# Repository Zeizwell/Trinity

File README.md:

# ZX Trinity

**Sound card for the ZX Spectrum: Atari, Amiga and MSX on one board.** For ZX-BUS / NemoBus and ZX Evolution.

| | |
|---|---|
| AY | 2 × AY-3-8910 / YM2149F in sockets, TurboSound (chip select `#FF` / `#FE`), ports `#FFFD` / `#BFFD` |
| AYFX | timer effects on the real AY chips: SID, Sync, FM, Env FM, PWM (16 steps 0..50 %, sweep) |
| SNDH | Atari ST music player: 68000 at 8 MHz on the card, sound on the real AY chips |
| GS | General Sound interface (`#B3` / `#BB`); NeoGS - in progress |
| Tracker modules | MOD (ProTracker), S3M, XM up to 32 channels; IT - in progress |
| Amiga | Paula A500 / A1200, BLEP, LED filter; presets Clean, A500, A1200, HiFi, Custom |
| MSX | Moonsound OPL4, MIDI (GM) - in progress |
| DAC | PCM5102A, I2S 32 bit |
| Output | 3.5 mm line out: AY through an OPA1656 mixer, DAC directly; narrow stereo - DIP switch |
| Processors | 2 × RP2350B (16 MB flash, 8 MB PSRAM each), CPLD EPM3128 with its own 32 MHz clock |
| Storage | microSD |
| Screen | any SPI TFT module on a cable: scopes, levels, what is playing, chip status, temperature, firmware versions |

## Paula

| | |
|---|---|
| Channels | 4, samples 8 bit signed |
| Rate | own per channel: note period at 3.55 MHz (PAL), no common output rate |
| Signal | steps (zero-order hold), sample never resampled; steps band-limited: minBLEP 16 × 16 |
| Volume | 0..64; 6-bit PWM - option, off by default |
| Stereo | hard: 0 + 3 left, 1 + 2 right |
| Filters (board values) | A500: low-pass 1st order 4.4 kHz; LED: low-pass 2nd order 3.1 kHz, Q 0.66, on the fly (`E0x`); high-pass ~5 Hz; A1200: no 4.4 kHz |
| Modes | Clean, A500, A1200, HiFi (cubic), Custom - on the fly |
| ProTracker | replayer one to one, PT quirks kept; Paula registers = pt2-clone on 80,595 modules |

## Status

### Done
- Board rev A2: schematic, placement and routing done, DRC clean; next - Gerbers and order (rev A1 was made, but unusable: edge connector defect)
- S3M player: matches OpenMPT on 8,394 of 8,459 modules (99.2 %); XM player (up to 32 channels): 35,160 of 35,458 (99.2 %) (on PC, every song played to the end)
- General Sound: ports, loading modules and effects, commands (tested without a Spectrum)
- Z80 API and SDK: find the card, settings, presets, CPU load, filter curves, versions
- CPLD firmware, first version: 91 of 128 macrocells, testbench passes; not yet on hardware

### Works on a test setup (ZX Evolution + RP2350 board)
- AY part: registers and timer effects; the FT2 tracker finds the card and uses the effects
- SNDH player: the Spectrum only sends the file. Wild Commander plugin: play, pause, seek, next track

### To do
- Build the first boards and test on a real Spectrum, CPLD on hardware
- Firmware updates from SD, driver program for the Spectrum
- OPL4, MIDI, NeoGS, IT player; XM: filters (`Zxx`), more than 32 channels
- CPU clock modes Economy / Normal / Turbo
- Output up to 96 kHz
- Trinity player program: all card modes, channel and pattern view, bass / treble

---

# ZX Trinity

**Звуковая карта для ZX Spectrum: Atari, Amiga и MSX на одной плате.** Для ZX-BUS / NemoBus и ZX Evolution.

| | |
|---|---|
| AY | 2 × AY-3-8910 / YM2149F на панельках, TurboSound (выбор чипа `#FF` / `#FE`), порты `#FFFD` / `#BFFD` |
| AYFX | таймерные эффекты на настоящих AY: SID, Sync, FM, Env FM, PWM (16 ступеней 0..50 %, свип) |
| SNDH | плеер музыки Atari ST: 68000 на 8 МГц на карте, звук на настоящих AY |
| GS | интерфейс General Sound (`#B3` / `#BB`); NeoGS - в работе |
| Трекерные модули | MOD (ProTracker), S3M, XM до 32 каналов; IT - в работе |
| Amiga | Paula A500 / A1200, BLEP, LED-фильтр; пресеты Clean, A500, A1200, HiFi, Custom |
| MSX | Moonsound OPL4, MIDI (GM) - в работе |
| ЦАП | PCM5102A, I2S 32 бита |
| Выход | линия 3.5 мм: AY через сумматор на OPA1656, ЦАП напрямую; узкое стерео - DIP-переключатель |
| Процессоры | 2 × RP2350B (флеш 16 МБ, PSRAM 8 МБ у каждого), CPLD EPM3128 со своим генератором 32 МГц |
| Носитель | microSD |
| Экран | любой SPI TFT-модуль на проводах: осциллографы, уровни, что играет, состояние чипов, температура, версии прошивок |

## Paula

| | |
|---|---|
| Каналы | 4, сэмплы 8 бит со знаком |
| Частота | своя у каждого канала: период ноты на 3.55 МГц (PAL), общей частоты вывода нет |
| Сигнал | ступеньки (удержание отсчёта), сэмпл не пересчитывается; ступеньки с ограниченной полосой: minBLEP 16 × 16 |
| Громкость | 0..64; ШИМ 6 бит - опция, по умолчанию выключен |
| Стерео | жёсткое: 0 + 3 слева, 1 + 2 справа |
| Фильтры (номиналы плат) | A500: ФНЧ 1-го порядка 4.4 кГц; LED: ФНЧ 2-го порядка 3.1 кГц, Q 0.66, на лету (`E0x`); ФВЧ ~5 Гц; A1200: без 4.4 кГц |
| Режимы | Clean, A500, A1200, HiFi (кубическая), Custom - на лету |
| ProTracker | реплеер один в один, причуды PT сохранены; регистры Paula = pt2-clone на 80 595 модулях |

## Что сейчас

### Готово
- Плата рев A2: схема, расстановка и разводка готовы, DRC чистый; дальше - гербера и заказ (рев A1 изготовлена, но не годится: брак разъёма шины)
- Плеер S3M: совпал с OpenMPT на 8 394 из 8 459 модулей (99.2 %); плеер XM (до 32 каналов): 35 160 из 35 458 (99.2 %) (на ПК, каждая песня до конца)
- General Sound: порты, загрузка модулей и эффектов, команды (проверено без Спектрума)
- API и SDK для Z80: поиск карты, настройки, пресеты, нагрузка, кривые фильтров, версии
- Прошивка CPLD, первая версия: 91 из 128 макроячеек, тест на модели проходит; на железе ещё нет

### Работает на макете (ZX Evolution + плата RP2350)
- Часть AY: регистры и таймерные эффекты; трекер FT2 находит карту и пользуется эффектами
- Плеер SNDH: Спектрум только отдаёт файл. Плагин для Wild Commander: игра, пауза, перемотка, следующий трек

### Дальше
- Собрать первые платы и проверить на настоящем Спектруме, CPLD на железе
- Обновление прошивок с SD, программа-драйвер для Спектрума
- OPL4, MIDI, NeoGS, плеер IT; XM: фильтры (`Zxx`), больше 32 каналов
- Режимы частоты процессора Эконом / Нормал / Турбо
- Вывод до 96 кГц
- Программа-плеер Trinity: все режимы карты, вид каналов и паттерна, НЧ / ВЧ

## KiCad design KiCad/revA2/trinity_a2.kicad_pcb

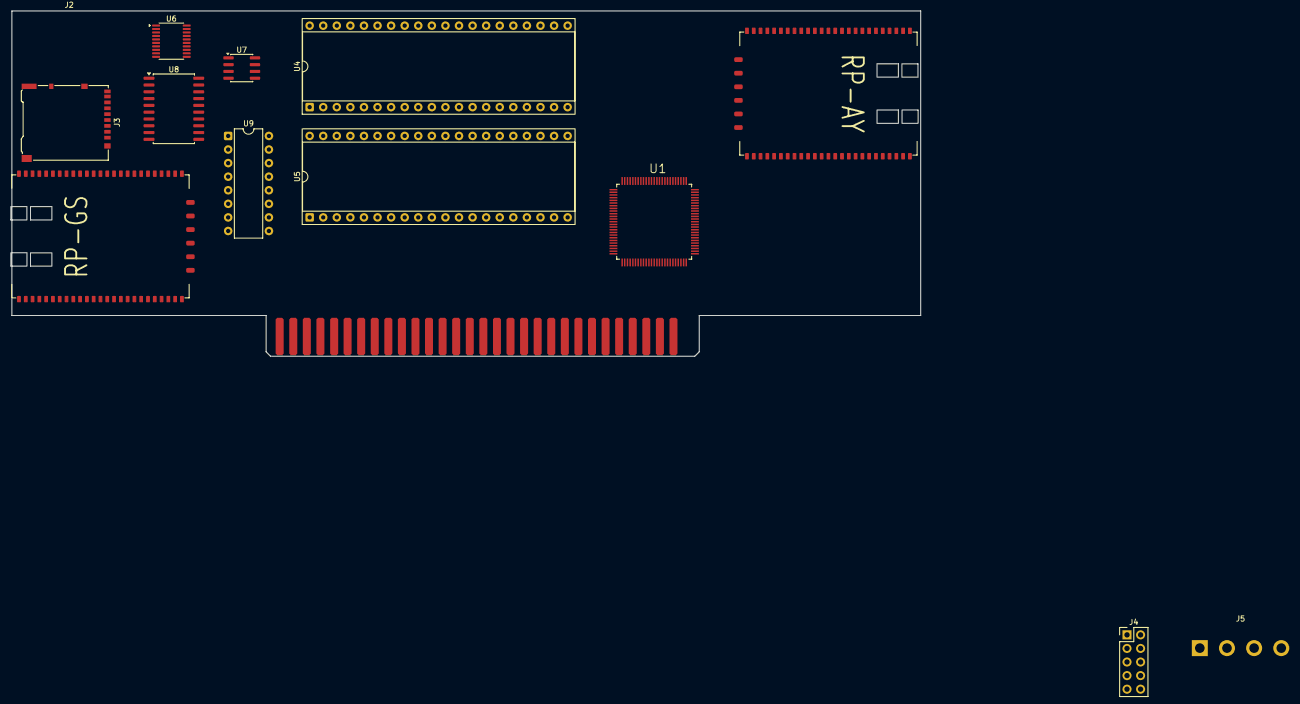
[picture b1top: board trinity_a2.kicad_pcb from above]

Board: 2 copper layers, 170.0 x 64.6 mm, 14 parts (0 on the bottom side), 2 nets, no tracks yet.

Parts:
J1: Conn_02x31_Row_Letter_First; ZX_NEMO_60_EDGE
J2: PJ-324M (линия); PJ-324M_placeholder
J3: microSD DM3AT; microSD_HC_Hirose_DM3AT-SF-PEJM5
J4: HD Audio (без 8); PinHeader_2x05_P2.54mm_Vertical
J5: Molex 4-pin; Molex_8981_4pin_placeholder
U1: EPM3128ATC100; QFP50P1600X1600X120-100N
U2: RP-GS; rp2350b
U3: RP-AY; rp2350b
U4, U5: AY-3-8910 / YM2149F; DIP-40_W15.24mm_Socket
U6: PCM5102A; TSSOP-20_4.4x6.5mm_P0.65mm
U7: NJM4580; SOIC-8_3.9x4.9mm_P1.27mm
U8: TPA6120A2 (DWP: + площадка снизу); SOIC-20W_7.5x12.8mm_P1.27mm
U9: 74HC4053; DIP-16_W7.62mm

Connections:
+5V: J1.a3, J1.a29, J1.b28
GND: J1.a6, J1.a7, J1.a14, J1.a30, J1.b30
